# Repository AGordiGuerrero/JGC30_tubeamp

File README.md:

# JGC30_tubeamp

"Small" guitar tube amplifier with two preamp channels.

It is conceived to be inserted in a small combo box with a single 12" speaker. 

Author: @AGordiGuerrero
        @SolEpcc
        University of Extremadura. Spain.
        
Features:
 - Two preamp channels:
      - Channel 1: Vox AC30 Top Boost type
      - Channel 2: Marshall JCM800 type
  - Around 10-15W of output power

Revision history:
  - V0.3: preamp PCB design with Kicad. It includes a supposedly well defined BOM.

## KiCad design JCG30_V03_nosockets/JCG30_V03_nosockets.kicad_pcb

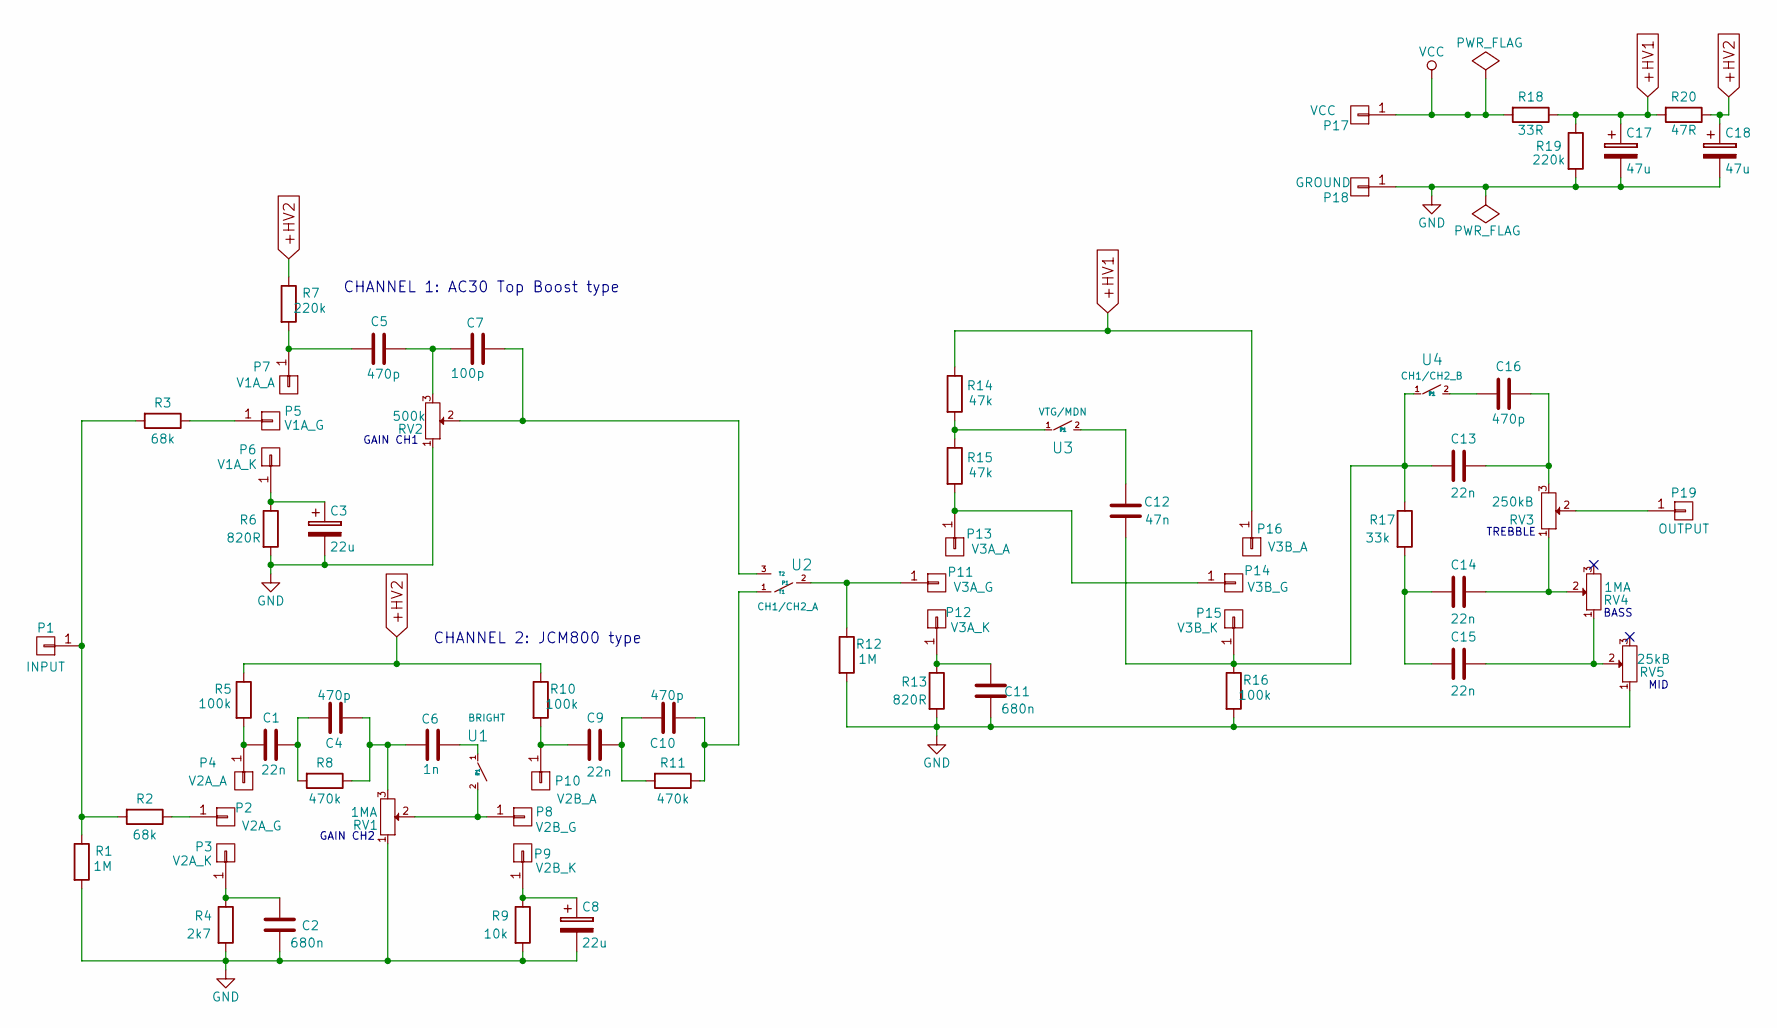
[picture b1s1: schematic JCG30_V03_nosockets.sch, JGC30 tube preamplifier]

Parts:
C1, C9, C13, C14, C15: 22n; C_Rect_L7_W3.5_P5
C2, C11: 680n; C_Rect_L7_W4.5_P5
C3, C8: 22u; C_Radial_D6.3_L11.2_P2.5
C4, C10: 470p; C_Rect_L7_W4.5_P5
C5, C16: 470p; C_Rect_L10_W2.5_P7.5
C6: 1n; C_Rect_L7_W4.5_P5
C7: 100p; C_Rect_L7_W4.5_P5
C12: 47n; C_Rect_L7_W4.5_P5
C17, C18: 47u; C_Radial_D14_L31.5_P5
P1: INPUT; SolderWirePad_single_1-5mmDrill
P2: V2A_G; SolderWirePad_single_1-5mmDrill
P3: V2A_K; SolderWirePad_single_1-5mmDrill
P4: V2A_A; SolderWirePad_single_1-5mmDrill
P5: V1A_G; SolderWirePad_single_1-5mmDrill
P6: V1A_K; SolderWirePad_single_1-5mmDrill
P7: V1A_A; SolderWirePad_single_1-5mmDrill
P8: V2B_G; SolderWirePad_single_1-5mmDrill
P9: V2B_K; SolderWirePad_single_1-5mmDrill
P10: V2B_A; SolderWirePad_single_1-5mmDrill
P11: V3A_G; SolderWirePad_single_1-5mmDrill
P12: V3A_K; SolderWirePad_single_1-5mmDrill
P13: V3A_A; SolderWirePad_single_1-5mmDrill
P14: V3B_G; SolderWirePad_single_1-5mmDrill
P15: V3B_K; SolderWirePad_single_1-5mmDrill
P16: V3B_A; SolderWirePad_single_1-5mmDrill
P17: VCC; SolderWirePad_single_1-5mmDrill
P18: GROUND; SolderWirePad_single_1-5mmDrill
P19: OUTPUT; SolderWirePad_single_1-5mmDrill
R1, R12: 1M; Resistor_Horizontal_RM10mm
R2, R3: 68k; Resistor_Horizontal_RM10mm
R4: 2k7; Resistor_Horizontal_RM10mm
R5, R10, R16: 100k; Resistor_Horizontal_RM10mm
R6, R13: 820R; Resistor_Horizontal_RM10mm
R7, R19: 220k; Resistor_Horizontal_RM10mm
R8, R11: 470k; Resistor_Horizontal_RM10mm
R9: 10k; Resistor_Horizontal_RM10mm
R14, R15: 47k; Resistor_Horizontal_RM10mm
R17: 33k; Resistor_Horizontal_RM10mm
R18: 33R; Resistor_Horizontal_RM10mm
R20: 47R; Resistor_Horizontal_RM10mm
RV1, RV4: 1MA; Potentiometer_WirePads_Small
RV2: 500k; Potentiometer_WirePads_Small
RV3: 250kB; Potentiometer_WirePads_Small
RV5: 25kB; Potentiometer_WirePads_Small
U1: BRIGHT; Socket_Strip_Straight_1x02
U2: CH1/CH2_A; Socket_Strip_Straight_1x03
U3: VTG/MDN; Socket_Strip_Straight_1x02
U4: CH1/CH2_B; Socket_Strip_Straight_1x02

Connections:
+HV1: C17.1, P16.1, R14.1, R18.1, R19.1, R20.2
+HV2: C18.1, R5.1, R7.1, R10.1, R20.1
GND: C2.1, C3.2, C8.2, C11.1, C17.2, C18.2, P18.1, R1.2, R4.2, R6.2, R9.2, R12.2, R13.2, R16.2, R19.2, RV1.1, RV2.1, RV5.1
unnamed: C1.1, C4.1, R8.2
unnamed: C1.2, P4.1, R5.2
unnamed: C2.2, P3.1, R4.1
unnamed: C3.1, P6.1, R6.1
unnamed: C4.2, C6.1, R8.1, RV1.3
unnamed: C5.1, C7.1, RV2.3
unnamed: C5.2, P7.1, R7.2
unnamed: C6.2, U1.1
unnamed: C7.2, RV2.2, U2.3 (T2)
unnamed: C8.1, P9.1, R9.1
unnamed: C9.2, P10.1, R10.2
unnamed: C9.1, C10.1, R11.2
unnamed: C10.2, R11.1, U2.1 (T1)
unnamed: C11.2, P12.1, R13.1
unnamed: C12.1, C13.2, P15.1, R16.1, R17.1, U4.1
unnamed: C12.2, U3.2 (T1)
unnamed: C13.1, C16.1, RV3.3
unnamed: C14.1, RV3.1, RV4.2
unnamed: C14.2, C15.2, R17.2
unnamed: C15.1, RV4.1, RV5.2
unnamed: C16.2, U4.2 (T1)
unnamed: P1.1, R1.1, R2.2, R3.2
unnamed: P2.1, R2.1
unnamed: P5.1, R3.1
unnamed: P8.1, RV1.2, U1.2 (T1)
unnamed: P11.1, R12.1, U2.2 (P1)
unnamed: P13.1, P14.1, R15.2
unnamed: P19.1, RV3.2
unnamed: R14.2, R15.1, U3.1
VCC: P17.1, R18.2

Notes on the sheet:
TREBBLE
BASS
MID
GAIN CH2
GAIN CH1
CHANNEL 1: AC30 Top Boost type
CHANNEL 2: JCM800 type

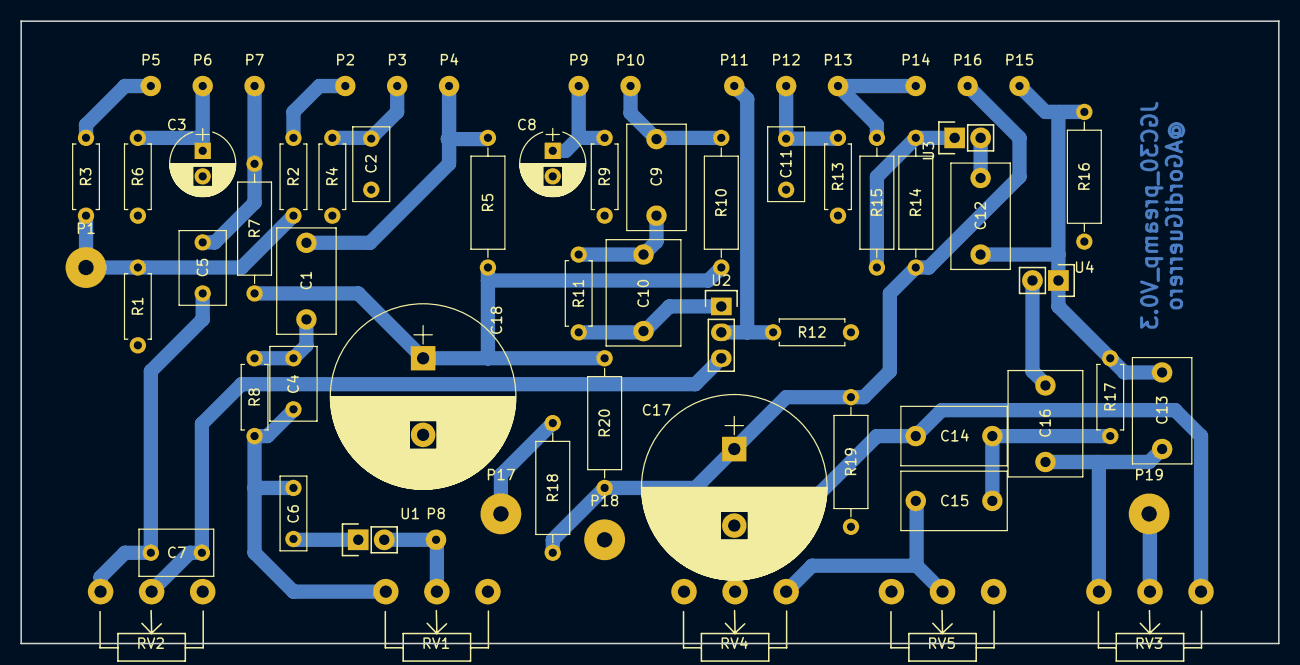
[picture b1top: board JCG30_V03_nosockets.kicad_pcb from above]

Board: 2 copper layers, 123.2 x 61.0 mm, 66 parts (0 on the bottom side), 33 nets.
